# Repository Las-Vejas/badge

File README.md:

<h1 align="center">
  <br>
  <a href="https://vejas.zip">
  </a>
  <br>
  <sub>VejasBadge</sub>
  <br>
</h1>

<div align="center">

</div>

<h4 align="center">An E-ink badge powered by the RP2040 MCU.</h4>

<br>

## Overview

VejasBadge is a compact wearable badge built around the Raspberry Pi **RP2040** microcontroller. It features an **E-ink display**, **NFC** via the ST25DV04K, and is powered over **USB-C** with battery charging support. 

It will be used to display info like my name, website and a photo of some sort. If the NFC coil works, I will add functionality, to choose the info transmitted by the NFC tag so you could share multiple website links. I would also like to use it as an ebook reader, but there may not be enough storage for that.

## Features

| Feature | Details |
|---------|---------|
| MCU | RP2040 @ 133MHz, LQFN-56 |
| Display | E-ink panel via 24-pin FPC connector (4-wire SPI) |
| NFC | ST25DV04K (ISO 15693 / I²C, 4Kbit) |
| Flash | ZD25WQ32CEIGR 32Mbit SPI Flash |
| RTC / Clock | ABM8-272-T3 crystal oscillator |
| Power | USB-C input, NCP1117ST33T3G 3.3V LDO|
| USB Protection | USBLC6-2SC6 ESD clamp |
| Buttons | 5× tactile switches (SKRKAEE020) |
| LEDs | 2× white status LEDs (0402) |

## Software

Firmware will be written in C++ using PlatformIO.

## Images

## Bill of Materials

### LCSC Components

| Part | Mfr. | Qty | Unit Price | Ext. Price | LCSC# |
|------|------|-----|------------|------------|-------|
| RP2040 | Raspberry Pi | 5 | $0.95 | $4.74 | [C2040](https://www.lcsc.com/product-detail/C2040.html) |
| ZD25WQ32CEIGR (32Mbit Flash) | Zetta | 5 | $0.57 | $2.86 | [C5258281](https://www.lcsc.com/product-detail/C5258281.html) |
| ST25DV04K-JFR6D3 (NFC) | ST | 5 | $0.86 | $4.30 | [C2654815](https://www.lcsc.com/product-detail/C2654815.html) |
| ABM8-272-T3 (Crystal) | ABRACON | 5 | $0.29 | $1.47 | [C20625731](https://www.lcsc.com/product-detail/C20625731.html) |
| NCP1117ST33T3G (LDO 3.3V) | onsemi | 5 | $0.24 | $1.18 | [C26537](https://www.lcsc.com/product-detail/C26537.html) |
| FPC-05F-24PH20 (24P FPC Connector) | XUNPU | 5 | $0.10 | $0.48 | [C2856805](https://www.lcsc.com/product-detail/C2856805.html) |
| USBLC6-2SC6 (ESD Protection) | HXY MOSFET | 5 | $0.03 | $0.16 | [C5261088](https://www.lcsc.com/product-detail/C5261088.html) |
| SI1308EDL (N-MOSFET) | TECH PUBLIC | 5 | $0.08 | $0.42 | [C7603347](https://www.lcsc.com/product-detail/C7603347.html) |
| MBR0530 (Schottky Diode) | Shikues | 50 | $0.02 | $1.00 | [C475718](https://www.lcsc.com/product-detail/C475718.html) |
| LB2012T680M (68µH Inductor) | Taiyo Yuden | 10 | $0.05 | $0.47 | [C223256](https://www.lcsc.com/product-detail/C223256.html) |
| YLED0402W (White LED) | YONGYUTAI | 50 | $0.015 | $0.77 | [C28310435](https://www.lcsc.com/product-detail/C28310435.html) |
| SKRKAEE020 (Tactile Switch) | Alps Alpine | 35 | $0.13 | $4.67 | [C115357](https://www.lcsc.com/product-detail/C115357.html) |
| USB-C Receptacle 16P | SHOU HAN | 20 | $0.07 | $1.48 | [C2765186](https://www.lcsc.com/product-detail/C2765186.html) |
| Cap 100nF 0402 | YAGEO | 100 | $0.001 | $0.13 | [C60474](https://www.lcsc.com/product-detail/C60474.html) |
| Cap 15pF 0402 NP0 | YAGEO | 100 | $0.001 | $0.13 | [C106997](https://www.lcsc.com/product-detail/C106997.html) |
| Cap 33pF 0402 NP0 | YAGEO | 100 | $0.001 | $0.13 | [C107005](https://www.lcsc.com/product-detail/C107005.html) |
| Cap 1µF 10V 0402 | Samsung EM | 100 | $0.003 | $0.30 | [C14445](https://www.lcsc.com/product-detail/C14445.html) |
| Cap 4.7µF 10V 0402 | Samsung EM | 50 | $0.008 | $0.39 | [C368809](https://www.lcsc.com/product-detail/C368809.html) |
| Cap 10µF 10V 0402 | Samsung EM | 20 | $0.012 | $0.23 | [C315248](https://www.lcsc.com/product-detail/C315248.html) |
| Res 3Ω 0402 | YAGEO | 100 | $0.002 | $0.20 | [C227064](https://www.lcsc.com/product-detail/C227064.html) |
| Res 27Ω 0402 | YAGEO | 100 | $0.001 | $0.09 | [C138021](https://www.lcsc.com/product-detail/C138021.html) |
| Res 1kΩ 0402 | YAGEO | 100 | $0.001 | $0.09 | [C106235](https://www.lcsc.com/product-detail/C106235.html) |
| Res 5.1kΩ 0402 | YAGEO | 100 | $0.001 | $0.09 | [C105872](https://www.lcsc.com/product-detail/C105872.html) |
| Res 10kΩ 0402 | YAGEO | 100 | $0.001 | $0.09 | [C60490](https://www.lcsc.com/product-detail/C60490.html) |

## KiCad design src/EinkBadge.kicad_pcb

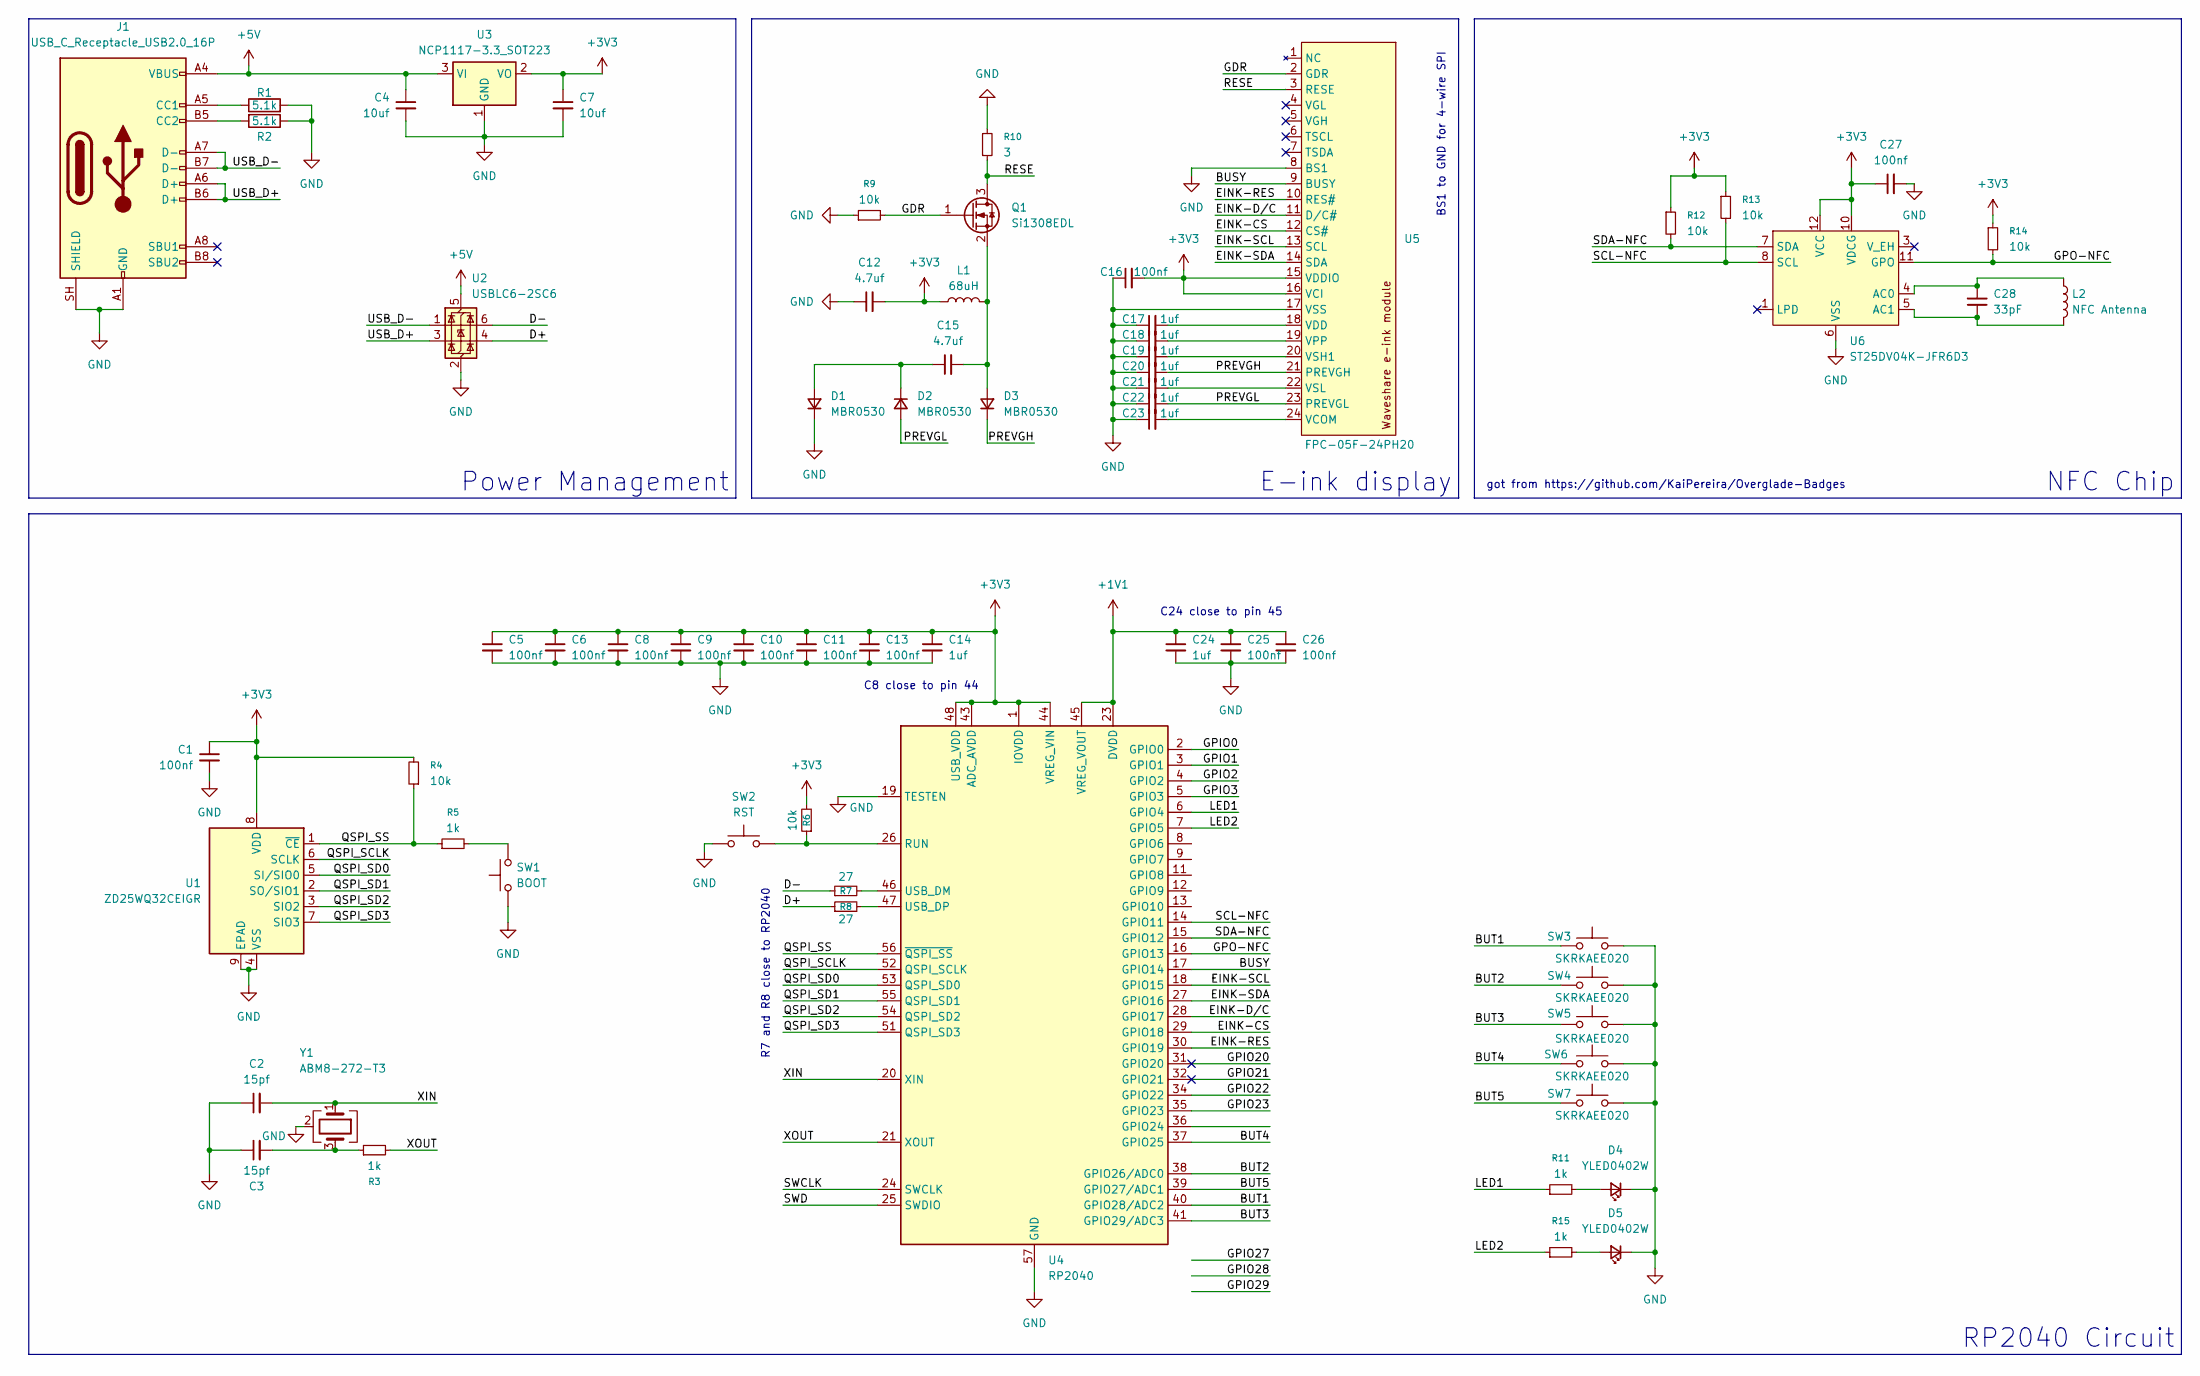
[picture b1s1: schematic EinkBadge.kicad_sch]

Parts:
C1, C5, C6, C8, C9, C10, C11, C13, C16, C25, C26, C27: 100nf; C_0402_1005Metric
C2, C3: 15pf; C_0402_1005Metric
C4, C7: 10uf; C_0402_1005Metric
C12, C15: 4.7uf; C_0402_1005Metric
C14, C17, C18, C19, C20, C21, C22, C23, C24: 1uf; C_0402_1005Metric
C28: 33pF; C_0402_1005Metric
D1, D2, D3: MBR0530; D_SOD-123
D4, D5: YLED0402W; LED_0402_1005Metric
J1: USB_C_Receptacle_USB2.0_16P; USB_C_Receptacle_GCT_USB4105-xx-A_16P_TopMnt_Horizontal
L1: 68uH; L_0805_2012Metric
L2: NFC Antenna; eink_badge_nfc5
Q1: Si1308EDL; SOT-323_SC-70
R1, R2: 5.1k; R_0402_1005Metric
R3, R5, R11, R15: 1k; R_0402_1005Metric
R4, R6, R9, R12, R13, R14: 10k; R_0402_1005Metric
R7, R8: 27; R_0402_1005Metric
R10: 3; R_0402_1005Metric
SW1: BOOT; SW_Push_SPST_NO_Alps_SKRK
SW2: RST; SW_Push_SPST_NO_Alps_SKRK
SW3, SW4, SW5, SW6, SW7: SKRKAEE020; SW_Push_SPST_NO_Alps_SKRK
U1: ZD25WQ32CEIGR; Winbond_USON-8-1EP_3x2mm_P0.5mm_EP0.2x1.6mm
U2: USBLC6-2SC6; SOT-23-6
U3: NCP1117-3.3_SOT223; SOT-223-3_TabPin2
U4: RP2040; QFN-56-1EP_7x7mm_P0.4mm_EP3.2x3.2mm
U5: FPC-05F-24PH20; TE_2-1734839-4_1x24-1MP_P0.5mm_Horizontal
U6: ST25DV04K-JFR6D3; ST_UFDFPN-12-1EP_3x3mm_P0.5mm_EP1.4x2.55mm
Y1: ABM8-272-T3; Crystal_SMD_3225-4Pin_3.2x2.5mm

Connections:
+1V1: C24.1, C25.1, C26.1, U4.23 (DVDD), U4.45 (VREG_VOUT), U4.50 (DVDD)
+3V3: C1.1, C5.1, C6.1, C7.1, C8.1, C9.1, C10.1, C11.1, C12.2, C13.1, C14.1, C16.2, C27.1, L1.1, R4.2, R6.2, R12.1, R13.1, R14.1, U1.8 (VDD), U3.2 (VO), U4.1 (IOVDD), U4.10 (IOVDD), U4.22 (IOVDD), U4.33 (IOVDD), U4.42 (IOVDD), U4.43 (ADC_AVDD), U4.44 (VREG_VIN), U4.48 (USB_VDD), U4.49 (IOVDD), U5.15 (VDDIO), U5.16 (VCI), U6.10 (VDCG), U6.12 (VCC)
+5V: C4.1, J1.A4 (VBUS), J1.A9 (VBUS), J1.B4 (VBUS), J1.B9 (VBUS), U2.5 (VBUS), U3.3 (VI)
/BUSY: U4.17 (GPIO14), U5.9 (BUSY)
/BUT1: SW3.1, U4.40 (GPIO28/ADC2)
/BUT2: SW4.1, U4.38 (GPIO26/ADC0)
/BUT3: SW5.1, U4.41 (GPIO29/ADC3)
/BUT4: SW6.1, U4.37 (GPIO25)
/BUT5: SW7.1, U4.39 (GPIO27/ADC1)
/D+: R8.1, U2.4 (I/O2)
/D-: R7.1, U2.6 (I/O1)
/EINK-CS: U4.29 (GPIO18), U5.12 (CS#)
/EINK-D/C: U4.28 (GPIO17), U5.11 (D/C#)
/EINK-RES: U4.30 (GPIO19), U5.10 (RES#)
/EINK-SCL: U4.18 (GPIO15), U5.13 (SCL)
/EINK-SDA: U4.27 (GPIO16), U5.14 (SDA)
/GDR: Q1.1 (G), R9.2, U5.2 (GDR)
/GPIO0: U4.2 (GPIO0)
/GPIO1: U4.3 (GPIO1)
/GPIO2: U4.4 (GPIO2)
/GPIO3: U4.5 (GPIO3)
/GPIO20: U4.31 (GPIO20)
/GPIO21: U4.32 (GPIO21)
/GPIO22: U4.34 (GPIO22)
/GPIO23: U4.35 (GPIO23)
/GPO-NFC: R14.2, U4.16 (GPIO13), U6.11 (GPO)
/LED1: R11.1, U4.6 (GPIO4)
/LED2: R15.1, U4.7 (GPIO5)
/PREVGH: C20.2, D3.1 (K), U5.21 (PREVGH)
/PREVGL: C22.2, D2.2 (A), U5.23 (PREVGL)
/QSPI_SCLK: U1.6 (SCLK), U4.52 (QSPI_SCLK)
/QSPI_SD0: U1.5 (SI/SIO0), U4.53 (QSPI_SD0)
/QSPI_SD1: U1.2 (SO/SIO1), U4.55 (QSPI_SD1)
/QSPI_SD2: U1.3 (SIO2), U4.54 (QSPI_SD2)
/QSPI_SD3: U1.7 (SIO3), U4.51 (QSPI_SD3)
/QSPI_SS: R4.1, R5.1, U1.1 (~CE), U4.56 (~QSPI_SS)
/RESE: Q1.3 (D), R10.2, U5.3 (RESE)
/SCL-NFC: R13.2, U4.14 (GPIO11), U6.8 (SCL)
/SDA-NFC: R12.2, U4.15 (GPIO12), U6.7 (SDA)
/SWCLK: U4.24 (SWCLK)
/SWD: U4.25 (SWDIO)
/USB_D+: J1.A6 (D+), J1.B6 (D+), U2.3 (I/O2)
/USB_D-: J1.A7 (D-), J1.B7 (D-), U2.1 (I/O1)
/XIN: C2.2, U4.20 (XIN), Y1.1
/XOUT: R3.2, U4.21 (XOUT)
GND: C1.2, C2.1, C3.1, C4.2, C5.2, C6.2, C7.2, C8.2, C9.2, C10.2, C11.2, C12.1, C13.2, C14.2, C16.1, C17.1, C18.1, C19.1, C20.1, C21.1, C22.1, C23.1, C24.2, C25.2, C26.2, C27.2, D1.1 (K), D4.1 (K), D5.1 (K), J1.A1 (GND), J1.A12 (GND), J1.B1 (GND), J1.B12 (GND), J1.SH (SHIELD), R1.2, R2.1, R9.1, R10.1, SW1.1, SW2.1, SW3.2, SW4.2, SW5.2, SW6.2, SW7.2, U1.4 (VSS), U1.9 (EPAD), U2.2 (GND), U3.1 (GND), U4.19 (TESTEN), U4.57 (GND), U5.8 (BS1), U5.17 (VSS), U6.6 (VSS), Y1.2 (G), Y1.4 (G)
unnamed: C3.2, R3.1, Y1.3
unnamed: C15.1, D1.2 (A), D2.1 (K)
unnamed: C15.2, D3.2 (A), L1.2, Q1.2 (S)
unnamed: D4.2 (A), R11.2
unnamed: D5.2 (A), R15.2
unnamed: J1.A5 (CC1), R1.1
unnamed: J1.B5 (CC2), R2.2
unnamed: R5.2, SW1.2
unnamed: R6.1, SW2.2, U4.26 (RUN)
unnamed: R7.2, U4.46 (USB_DM)
unnamed: R8.2, U4.47 (USB_DP)
unnamed: C23.2, U5.24 (VCOM)
unnamed: C17.2, U5.18 (VDD)
unnamed: C18.2, U5.19 (VPP)
unnamed: C19.2, U5.20 (VSH1)
unnamed: C21.2, U5.22 (VSL)
unnamed: C28.2, L2.1, U6.4 (AC0)
unnamed: C28.1, L2.2, U6.5 (AC1)

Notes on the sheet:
R7 and R8 close to RP2040
got from https://github.com/KaiPereira/Overglade-Badges
C24 close to pin 45
C8 close to pin 44
BS1 to GND for 4-wire SPI
RP2040 Circuit
Power Management
E-ink display
NFC Chip

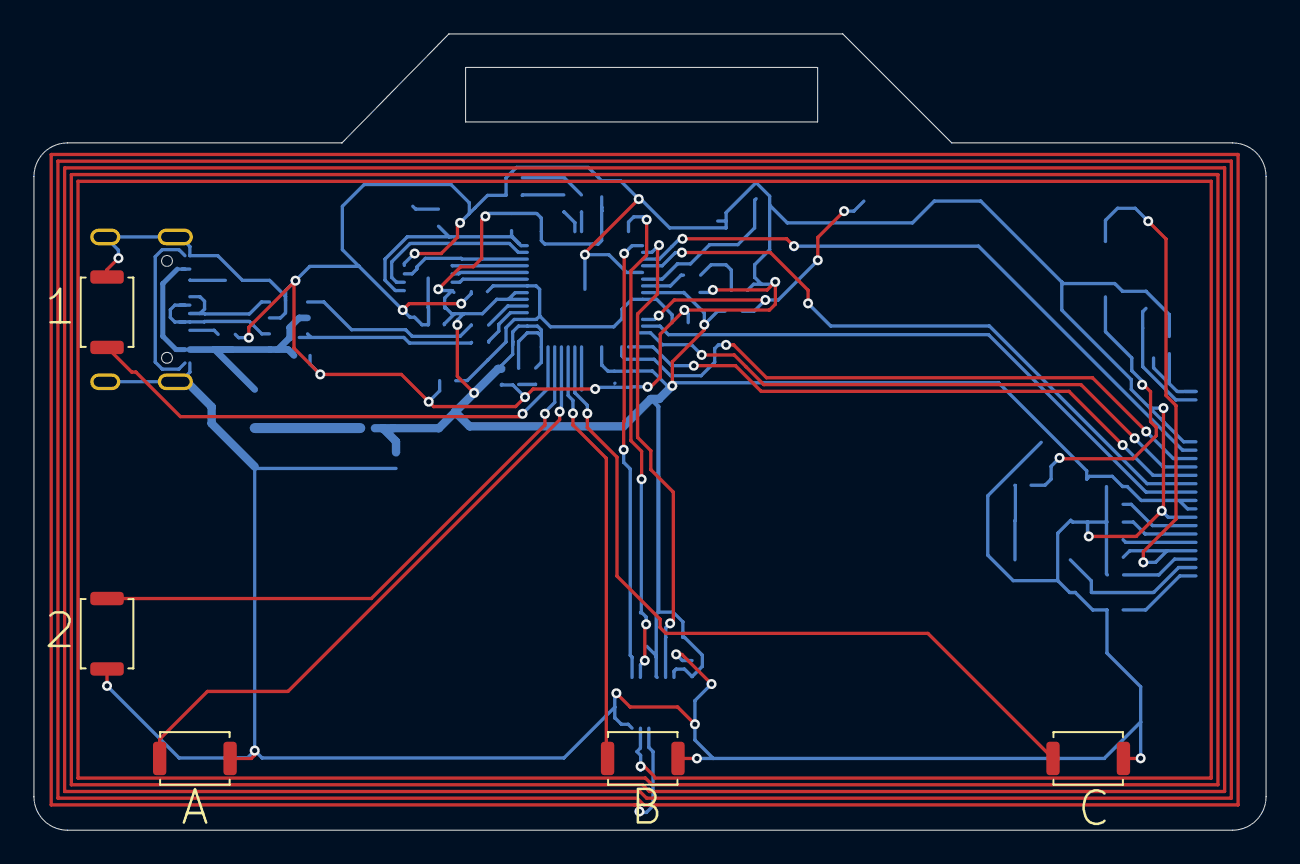
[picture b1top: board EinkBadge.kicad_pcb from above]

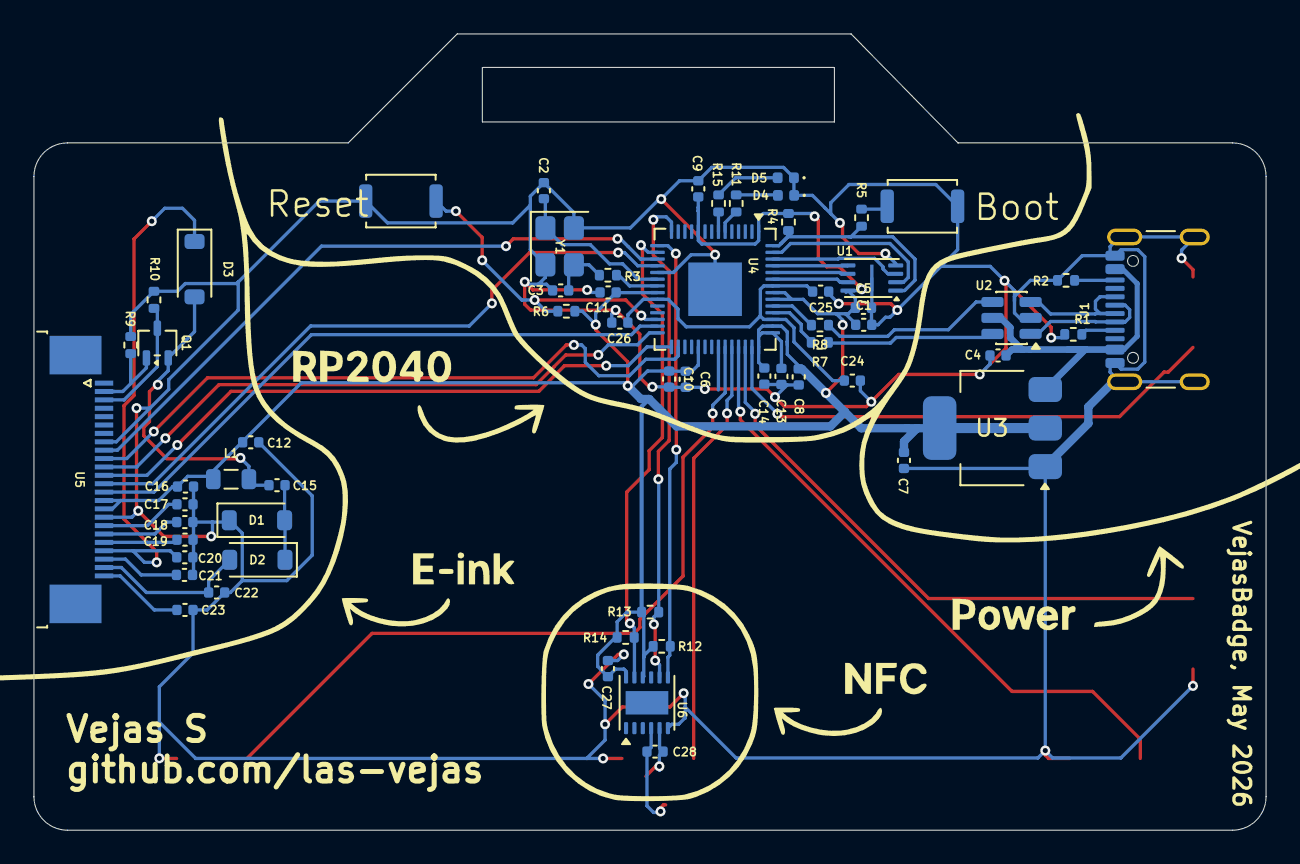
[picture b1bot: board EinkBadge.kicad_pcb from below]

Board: 2 copper layers, 73.5 x 47.5 mm, 66 parts (60 on the bottom side), 54 nets.

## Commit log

2026-05-28 added pcb
